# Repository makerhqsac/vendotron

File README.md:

# vendotron
Vendotron Internet Vending Machine

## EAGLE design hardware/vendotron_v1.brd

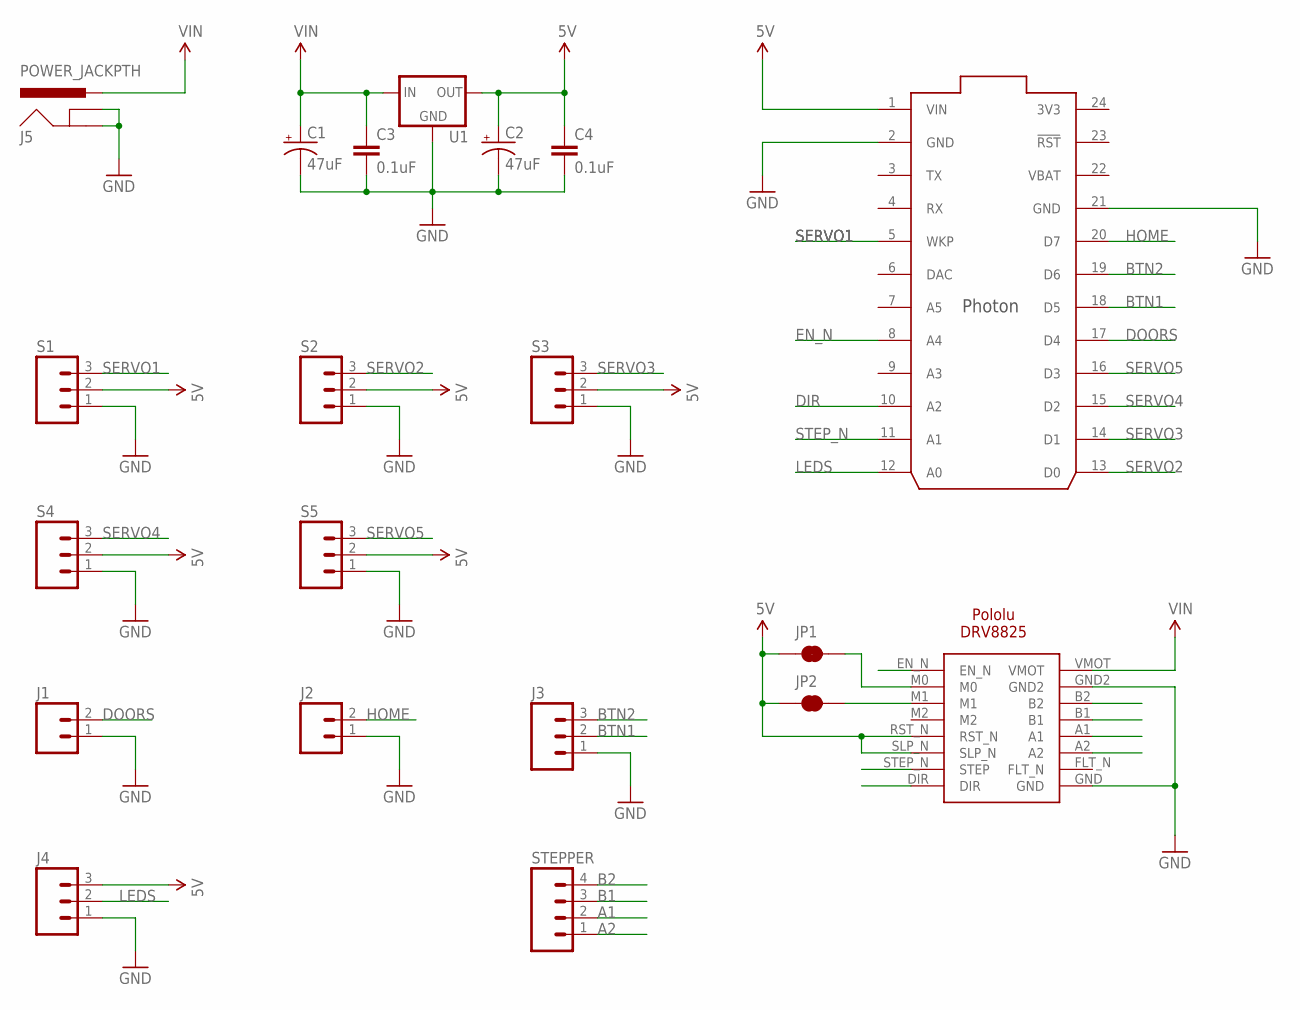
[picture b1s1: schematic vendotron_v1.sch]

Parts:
C1, C2: 47uF; CPOL-RADIAL-10UF-25V
C3, C4: 0.1uF; CAP-PTH-SMALL
J1, J2: M023.5MM; SCREWTERMINAL-3.5MM-2
J3, J4: M03SCREW; SCREWTERMINAL-3.5MM-3
J5: POWER_JACKPTH; POWER_JACK_PTH
JP1, JP2: JUMPER-PAD-2-NC_BY_TRACE; PAD-JUMPER-2-NC_BY_TRACE_YES_SILK
S1, S2, S3, S4, S5: M03PTH; 1X03
STEPPER: M04SCREW; SCREWTERMINAL-3.5MM-4
U1: V_REG_78XXSINK; TO220-IGO
U$1: PHOTON_WITH_HEADERS; PHOTON
U$2: POLOLU-DRV8825

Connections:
3V3: U$1.24 (3V3)
5V: C2.1 (+), C4.1, J4.3, JP1.1, JP2.1, S1.2, S2.2, S3.2, S4.2, S5.2, U1.OUT, U$1.1 (VIN), U$2.RST_N, U$2.SLP_N
A1: STEPPER.2, U$2.A1
A2: STEPPER.1, U$2.A2
B1: STEPPER.3, U$2.B1
B2: STEPPER.4, U$2.B2
BTN1: J3.2, U$1.18 (D5)
BTN2: J3.3, U$1.19 (D6)
DIR: U$1.10 (A2), U$2.DIR
DOORS: J1.2, U$1.17 (D4)
EN_N: U$1.8 (A4), U$2.EN_N
GND: C1.2 (-), C2.2 (-), C3.2, C4.2, J1.1, J2.1, J3.1, J4.1, J5.GND, J5.GNDBREAK, S1.1, S2.1, S3.1, S4.1, S5.1, U1.GND, U$1.2 (GND), U$1.21 (GND), U$2.GND, U$2.GND2
HOME: J2.2, U$1.20 (D7)
LEDS: J4.2, U$1.12 (A0)
unnamed: JP1.2, U$2.M0
unnamed: JP2.2, U$2.M1
SERVO1: S1.3, U$1.5 (WKP)
SERVO2: S2.3, U$1.13 (D0)
SERVO3: S3.3, U$1.14 (D1)
SERVO4: S4.3, U$1.15 (D2)
SERVO5: S5.3, U$1.16 (D3)
STEP_N: U$1.11 (A1), U$2.STEP_N (STEP)
VBAT: U$1.22 (VBAT)
VIN: C1.1 (+), C3.1, J5.PWR, U1.IN, U$2.VMOT

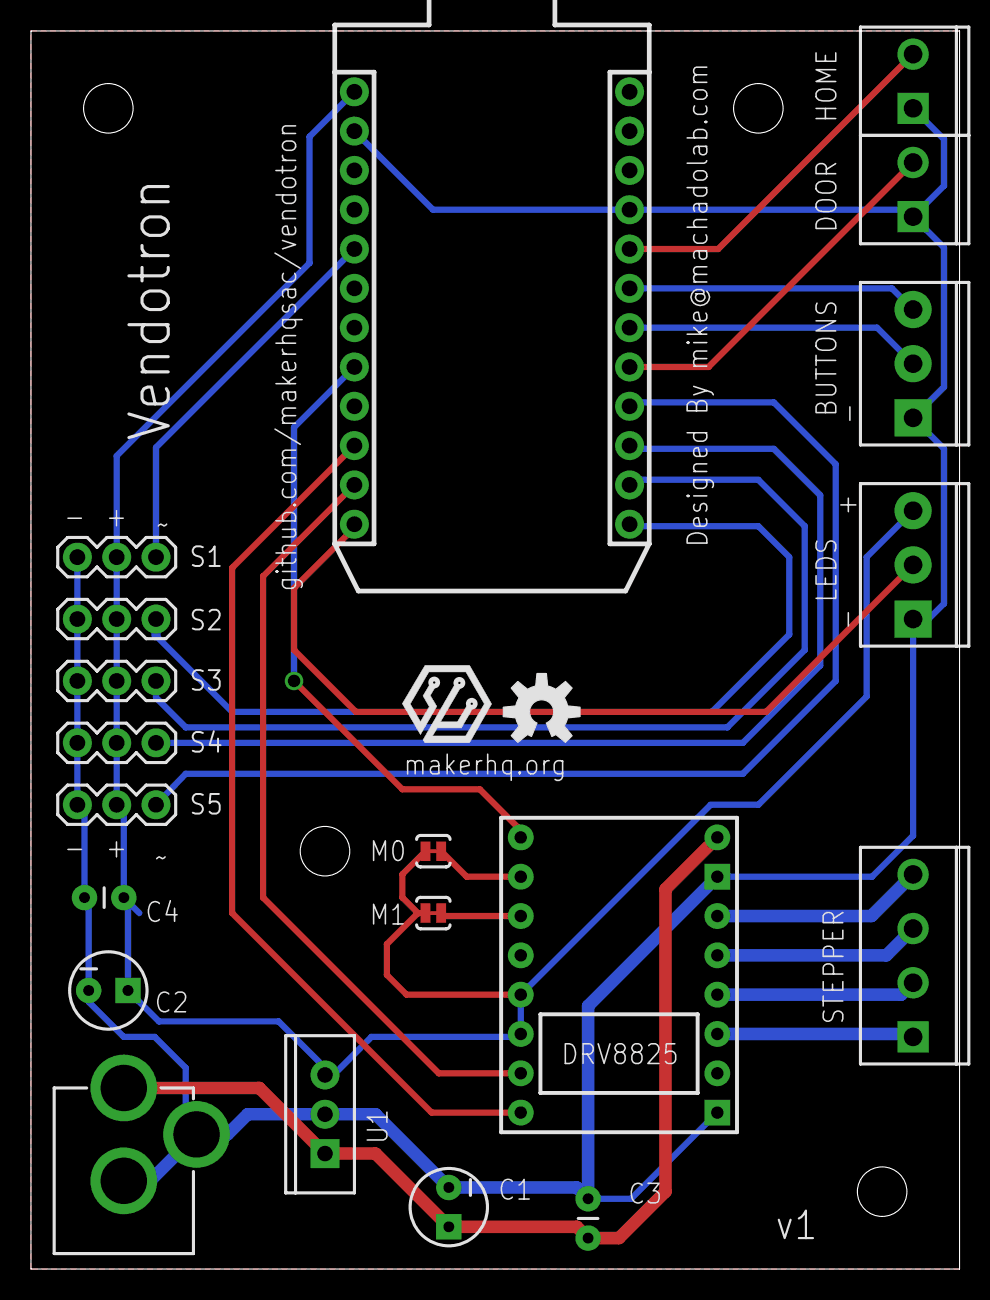
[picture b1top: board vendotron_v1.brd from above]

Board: 2 copper layers, 60.0 x 80.0 mm, 22 parts (0 on the bottom side), 22 nets.

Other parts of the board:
U$3: MAKERHQ_LOGO_L
U$4: OSHW-LOGO-M

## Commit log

2016-07-23 Add hardware files
2016-07-26 rename files
2016-07-26 Add CAD model
2016-07-31 cad updates
2016-10-10 Add DXF files
2017-07-15 Create LICENSE

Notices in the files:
parts and their libraries:
SparkFun-Connectors: Licensing: Creative Commons ShareAlike 4.0 International - https://creativecommons.org/licenses/by-sa/4.0
